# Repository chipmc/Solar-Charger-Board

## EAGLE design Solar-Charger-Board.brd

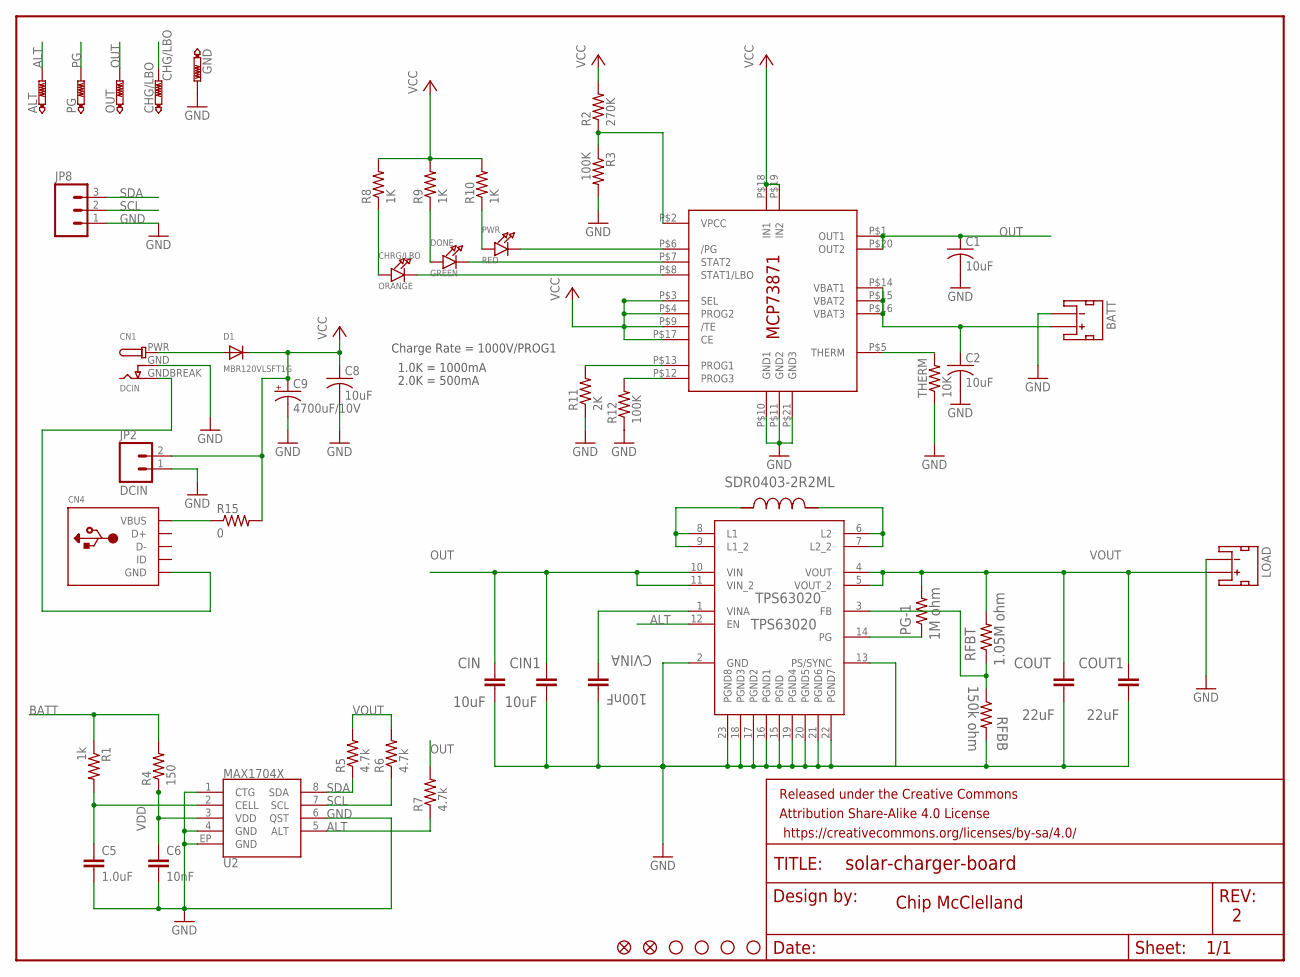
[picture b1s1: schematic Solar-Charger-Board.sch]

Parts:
ALT: PTR1TP09R; TP09R
BATT: JST_2MM_MALE; JST-2-SMD
C1, C2, C8: 10uF; C0805K
C5: 1.0uF; 0805
C6: 10nF; 0805
C9: 4700uF/10V; E5-13
CHG/LBO: PTR1TP09R; TP09R
CHRG/LBO: ORANGE; CHIPLED_0805_NOOUTLINE
CIN, CIN1: 10uF; 0805
CN1: DCIN; DCJACK_2MM_SMT
CN4: USBMINIBLARGE; USB-MINIB_LARGER
COUT, COUT1: 22uF; 0805
CVINA: 100nF; 0805
D1: MBR120VLSFT1G; SOD-123
DONE: GREEN; CHIPLED_0805_NOOUTLINE
FID1, FID2: FIDUCIALUFIDUCIAL; MICRO-FIDUCIAL
FRAME2: FRAME-LETTER; CREATIVE_COMMONS
GND: PTR1TP09R; TP09R
JP2: DCIN; 1X02_LOCK
JP3, JP4, JP5, JP6: STAND-OFF
JP8: M03LOCK; 1X03_LOCK
L1: SDR0403-2R2ML; SDR0403
LOAD: JST_2MM_MALE; JST-2-SMD
MAX1704X: U2; TDFN-8
MCP73871: U1; QFN20_4MM
OUT: PTR1TP09R; TP09R
PG: PTR1TP09R; TP09R
PG-1: 1M ohm; 0805
PWR: RED; CHIPLED_0805_NOOUTLINE
R1: 1k; 0805
R2: 270K; R0805
R3: 100K; R0805
R4: 150; 0805
R5, R6, R7: 4.7k; 0805
R8, R9, R10: 1K; R0805
R11: 2K; 0805
R12: 100K; 0805
R15: 0; R0805
RFBB: 150k ohm; 0805
RFBT: 1.05M ohm; 0805
THERM: 10K; 0805
TPS63020: TPS63020; QFN14-3X4MM

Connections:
ALT: ALT.TP, MAX1704X.5 (ALT), R7.1, TPS63020.12 (EN)
BATT: BATT.2 (+), C2.1, MCP73871.P$14 (VBAT1), MCP73871.P$15 (VBAT2), MCP73871.P$16 (VBAT3), R1.1, R4.2
CHG/LBO: CHG/LBO.TP, CHRG/LBO.C, MCP73871.P$8 (STAT1/LBO)
DONE: DONE.C, MCP73871.P$7 (STAT2)
FB: RFBB.1, RFBT.1, TPS63020.3 (FB)
GND: BATT.1 (-), C1.2, C2.2, C5.2, C6.2, C8.2, C9.-, CIN.2, CIN1.2, CN1.GND (GNDBREAK), COUT.2, COUT1.2, CVINA.2, GND.TP, JP2.1, JP8.1, LOAD.1 (-), MAX1704X.1 (CTG), MAX1704X.4 (GND), MAX1704X.6 (QST), MAX1704X.EP (GND), MCP73871.P$10 (GND1), MCP73871.P$11 (GND2), MCP73871.P$21 (GND3), R3.2, R11.1, R12.1, RFBB.2, THERM.1, TPS63020.2 (GND), TPS63020.13 (PS/SYNC), TPS63020.15 (PGND), TPS63020.16 (PGND1), TPS63020.17 (PGND2), TPS63020.18 (PGND3), TPS63020.19 (PGND4), TPS63020.20 (PGND5), TPS63020.21 (PGND6), TPS63020.22 (PGND7), TPS63020.23 (PGND8)
unnamed: L1.1, TPS63020.8 (L1), TPS63020.9 (L1_2)
unnamed: C5.1, MAX1704X.2 (CELL), R1.2
unnamed: L1.2, TPS63020.6 (L2), TPS63020.7 (L2_2)
unnamed: CN4.VBUS, R15.1
unnamed: MCP73871.P$2 (VPCC), R2.1, R3.1
unnamed: CVINA.1, TPS63020.1 (VINA)
unnamed: MCP73871.P$5 (THERM), THERM.2
unnamed: CN1.PWR, D1.A
unnamed: CHRG/LBO.A, R8.1
unnamed: DONE.A, R9.1
unnamed: PWR.A, R10.1
unnamed: MCP73871.P$12 (PROG3), R12.2
unnamed: MCP73871.P$13 (PROG1), R11.2
unnamed: CN1.GNDBREAK (GND), CN4.GND, CN4.GND1 (GND), CN4.GND2 (GND), CN4.GND3 (GND), CN4.GND4 (GND)
OUT: C1.1, CIN.1, CIN1.1, MCP73871.P$1 (OUT1), MCP73871.P$20 (OUT2), OUT.TP, R7.2, TPS63020.10 (VIN), TPS63020.11 (VIN_2)
PG: PG.TP, PG-1.1, TPS63020.14 (PG)
PWR: MCP73871.P$6 (/PG), PWR.C
SCL: JP8.2, MAX1704X.7 (SCL), R6.1
SDA: JP8.3, MAX1704X.8 (SDA), R5.1
VCC: C8.1, C9.+, D1.C, JP2.2, MCP73871.P$3 (SEL), MCP73871.P$4 (PROG2), MCP73871.P$9 (/TE), MCP73871.P$17 (CE), MCP73871.P$18 (IN1), MCP73871.P$19 (IN2), R2.2, R8.2, R9.2, R10.2, R15.2
VDD: C6.1, MAX1704X.3 (VDD), R4.1
VOUT: COUT.1, COUT1.1, LOAD.2 (+), PG-1.2, R5.2, R6.2, RFBT.2, TPS63020.4 (VOUT), TPS63020.5 (VOUT_2)

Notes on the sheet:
Charge Rate = 1000V/PROG1
1.0K = 1000mA
2.0K = 500mA
Chip McClelland

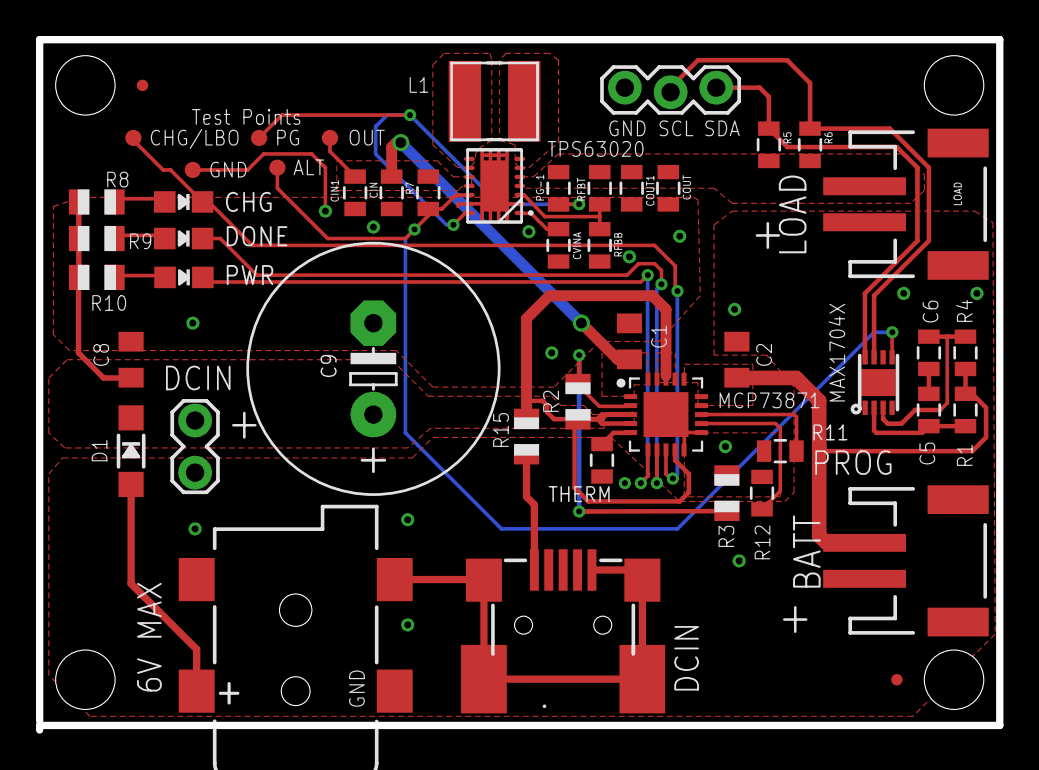
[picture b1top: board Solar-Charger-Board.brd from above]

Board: 2 copper layers, 53.3 x 38.4 mm, 54 parts (0 on the bottom side), 28 nets.

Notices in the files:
parts and their libraries:
SparkFun-Connectors: Licensing: Creative Commons ShareAlike 4.0 International - https://creativecommons.org/licenses/by-sa/4.0
SparkFun-Aesthetics: Released under the Creative Commons Attribution Share-Alike 4.0 License
SparkFun-Aesthetics: https://creativecommons.org/licenses/by-sa/4.0
